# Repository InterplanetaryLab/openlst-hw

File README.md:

Interplanetary Initiative Lab Fork - OpenLST Reference Hardware
==========================
Due to the Qorvo Power Amplifier in the original design being deprecated, 
the power amplifier was swapped to the newer Qorovo RFFM6406. 
This was more of just a name change as the pinout is identical and the 
electrical specifications of both chips are nearly identical.

*Note - Gerbel files should not need to be updated *

OpenLST Reference Hardware
==========================

This repository contains a KiCad project with a hardware reference
implementation for the OpenLST.  This design is a simplified version
of the Texas Instruments CC1110 432 MHz reference design.  A 1 watt
power amplifier module has been added to increase operating range.
The design is intended for use at 437 MHz, however, it may be modified
for use at other frequencies.

The user is responsible for obtaining and maintaining the necessary
license to operate this radio.  The example project uses frequencies
in the US Amateur Radio UHF band. Transmissions in this band require a
valid FCC license and compliance with CFR Part 97.

Contents
--------

This repository contains the following items:

  * [KiCAD 4.0](http://kicad-pcb.org/) project with self-contained part library
  * [Schematic](pdf/openlst-hw.pdf) in PDF form
  * [Bill of materials](bom/) with ordering information for components
  * [Gerber files](gerber/) for PCB fabrication

License & Legal Information
---------------------------

Copyright 2018 Planet Labs Inc. This work is licensed under a
Creative Commons Attribution-ShareAlike 4.0 International License.

This document may contain technology or software the export of which
is or may be restricted by the Export Administration Act and the
Export Administration Regulations (EAR), 15 C.F.R. parts
730-774. Diversion contrary to U.S. law is prohibited.

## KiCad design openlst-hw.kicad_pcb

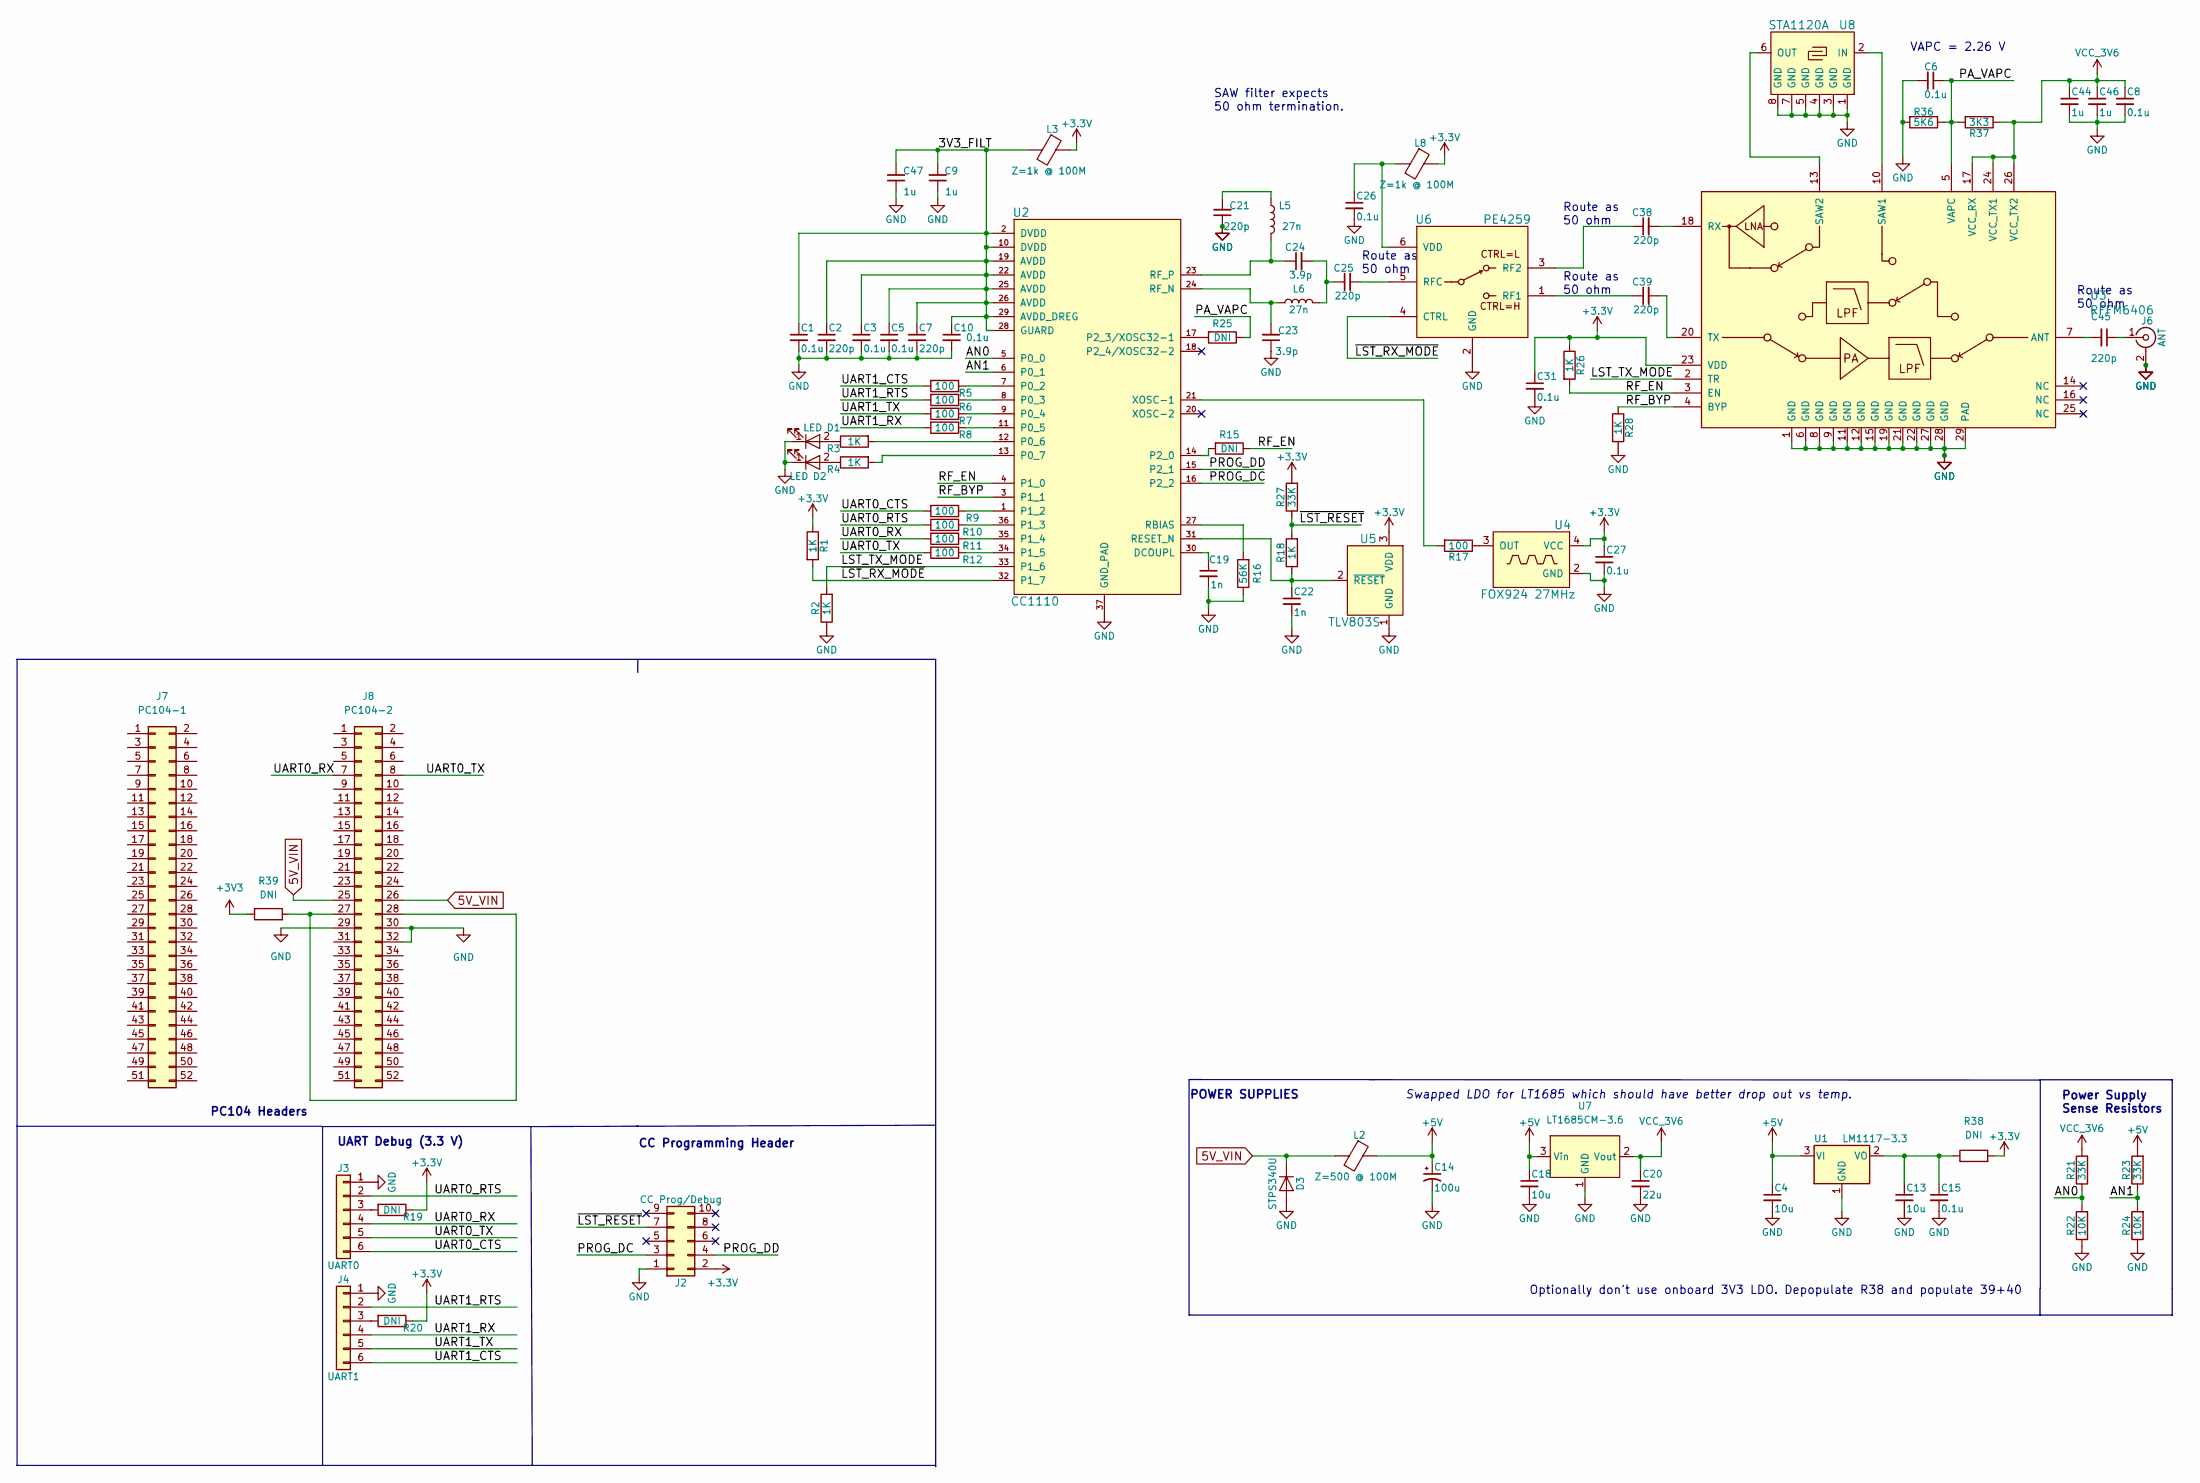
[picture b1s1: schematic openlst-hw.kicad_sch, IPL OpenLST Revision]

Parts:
C1, C3, C5, C6, C8, C10, C15, C26, C27, C31: 0.1u; C_0603_1608Metric; ManufPN 0603YC104K4T4A
C2, C7, C21, C25, C38, C39, C45: 220p; C_0402_1005Metric; ManufPN C0402C221J2GACAUTO
C4, C13, C18: 10u; C_0603_1608Metric; ManufPN GRT188C81A106ME13D
C9, C44, C46, C47: 1u; C_0603_1608Metric; ManufPN CL10B105MO8NNWC
C14: 100u; CP_EIA-3528-15_AVX-H; ManufPN TPSB107M010R0400
C19, C22: 1n; C_0603_1608Metric; ManufPN GCM188R71E102KA37D
C20: 22u; C_0603_1608Metric; ManufPN GRT188C81A106ME13D
C23, C24: 3.9p; C_0402_1005Metric; ManufPN GJM1555C1H3R9CB01D
D1: LED; LED_0603_1608Metric; ManufPN 150060VS75000
D2: LED; LED_0603_1608Metric; ManufPN 150060SS75000
D3: STPS340U; D_SMB; ManufPN STPS340U
J2: CC Prog/Debug; PinHeader_2x05_P1.27mm_Vertical_SMD; ManufPN FTSH-105-01-L-DV-K-P
J3: UART0; PinHeader_1x06_P2.54mm_Vertical; ManufPN 61300611121
J4: UART1; PinHeader_1x06_P2.54mm_Vertical; ManufPN 61300611121
J6: ANT; SMA_Amphenol_132134_Vertical; ManufPN 732511150
J7: PC104-1; PinSocket_2x26_P2.54mm_Vertical
J8: PC104-2; PinSocket_2x26_P2.54mm_Vertical
L2: Z=500 @ 100M; L_1206_3216Metric; ManufPN MI1206L501R-10
L3, L8: Z=1k @ 100M; L_0603_1608Metric; ManufPN 74279266
L5, L6: 27n; L_0402_1005Metric; ManufPN LQW15AN27NJ00D
R1, R2, R3, R4, R18, R26, R28: 1K; R_0603_1608Metric; ManufPN RC0603JR-071KL
R5, R6, R7, R8, R9, R10, R11, R12, R17: 100; R_0603_1608Metric; ManufPN AC0603FR-07100RL
R15, R19, R20, R25: DNI; R_0603_1608Metric
R16: 56K; R_0603_1608Metric; ManufPN RMCF0603FT56K0
R21, R23, R27: 33K; R_0603_1608Metric; ManufPN AC0603FR-0733KL
R22, R24: 10K; R_0603_1608Metric; ManufPN RC0603JR-0710KL
R36: 5K6; R_0603_1608Metric; ManufPN RMCF0603FT5K60
R37: 3K3; R_0603_1608Metric; ManufPN RMCF0603FT3K30
R38, R39: DNI; R_0603_1608Metric_Pad0.98x0.95mm_HandSolder
U1: LM1117-3.3; SOT-223-3_TabPin2; ManufPN LM1117IMP-3.3/NOPB
U2: CC1110; TI_CC_QFN36; ManufPN CC1110F32RHHR
U3: RFFM6406; Qorvo_LGA_28
U4: FOX924 27MHz; Oscillator_SMD_Fordahl_DFAS15-4Pin_5.0x3.2mm; ManufPN FT5HNBPK27.0-T1
U5: TLV803S; SOT-23; ManufPN TLV803SDBZR
U6: PE4259; SOT-363_SC-70-6; ManufPN 4259-63
U7: LT1685CM-3.6; TO-263-3_TabPin2
U8: STA1120A; SAW-8_3.8mm; ManufPN STA1120A

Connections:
5V_VIN: D3.1 (K), J8.25, J8.26, L2.2
+5V: C4.1, C14.1, C18.1, L2.1, R23.2, U1.3 (VI), U7.3 (Vin)
/3V3_FILT: C1.1, C2.1, C3.1, C5.1, C7.1, C9.2, C10.1, C47.2, L3.2, U2.2 (DVDD), U2.10 (DVDD), U2.19 (AVDD), U2.22 (AVDD), U2.25 (AVDD), U2.26 (AVDD), U2.28 (GUARD), U2.29 (AVDD_DREG)
/AN0: R21.1, R22.2, U2.5 (P0_0)
/AN1: R23.1, R24.2, U2.6 (P0_1)
/LST_TX_MODE: R2.2, U2.33 (P1_6), U3.2 (TR); also elsewhere on the board
/PA_VAPC: C6.1, R25.1, R36.1, R37.2, U3.5 (VAPC)
/PROG_DC: J2.3, U2.16 (P2_2)
/PROG_DD: J2.4, U2.15 (P2_1)
/RF_BYP: R28.1, U2.3 (P1_1), U3.4 (BYP)
/RF_EN: R15.1, R26.2, U2.4 (P1_0), U3.3 (EN)
/UART0_CTS: J3.6, R9.2
/UART0_RTS: J3.2, R10.2
/UART0_RX: J3.4, J8.7, R11.2
/UART0_TX: J3.5, J8.8, R12.2
/UART1_CTS: J4.6, R5.2
/UART1_RTS: J4.2, R6.2
/UART1_RX: J4.4, R8.2
/UART1_TX: J4.5, R7.2
/~LST_RESET: J2.7, R18.2, R27.1
/~LST_RX_MODE: R1.2, U2.32 (P1_7), U6.4 (CTRL); also elsewhere on the board
GND: C1.2, C2.2, C3.2, C4.2, C5.2, C6.2, C7.2, C8.2, C9.1, C10.2, C13.2, C14.2, C15.2, C18.2, C19.2, C20.2, C21.1, C22.2, C23.1, C26.2, C27.2, C31.2, C44.2, C46.2, C47.1, D1.1 (K), D2.1 (K), D3.2 (A), J2.1, J3.1, J4.1, J6.2 (Ext), J8.29, J8.30, J8.32, R2.1, R16.1, R22.1, R24.1, R28.2, R36.2, U1.1 (GND), U2.37 (GND_PAD), U3.1 (GND), U3.6 (GND), U3.8 (GND), U3.9 (GND), U3.11 (GND), U3.12 (GND), U3.15 (GND), U3.19 (GND), U3.21 (GND), U3.22 (GND), U3.27 (GND), U3.28 (GND), U3.29 (PAD), U4.2 (GND), U5.1 (GND), U6.2 (GND), U7.1 (GND), U8.1 (GND), U8.3 (GND), U8.4 (GND), U8.5 (GND), U8.7 (GND), U8.8 (GND); also elsewhere on the board
unnamed: C13.1, C15.1, R38.1, U1.2 (VO)
unnamed: C19.1, U2.30 (DCOUPL)
unnamed: C21.2, L5.1
unnamed: C22.1, R18.1, U2.31 (RESET_N), U5.2 (~RESET)
unnamed: C23.2, L6.1, U2.24 (RF_N)
unnamed: C24.1, L5.2, U2.23 (RF_P)
unnamed: C24.2, C25.1, L6.2
unnamed: C25.2, U6.5 (RFC)
unnamed: C26.1, L8.2, U6.6 (VDD)
unnamed: C38.1, U6.3 (RF2)
unnamed: C38.2, U3.18 (RX)
unnamed: C39.1, U6.1 (RF1)
unnamed: C39.2, U3.20 (TX)
unnamed: C45.1, J6.1 (In)
unnamed: C45.2, U3.7 (ANT)
unnamed: D1.2 (A), R3.1
unnamed: D2.2 (A), R4.1
unnamed: J3.3, R19.2
unnamed: J4.3, R20.2
unnamed: J8.27, J8.28, R39.2
unnamed: R3.2, U2.12 (P0_6)
unnamed: R4.2, U2.13 (P0_7)
unnamed: R5.1, U2.7 (P0_2)
unnamed: R6.1, U2.8 (P0_3)
unnamed: R7.1, U2.9 (P0_4)
unnamed: R8.1, U2.11 (P0_5)
unnamed: R9.1, U2.1 (P1_2)
unnamed: R10.1, U2.36 (P1_3)
unnamed: R11.1, U2.35 (P1_4)
unnamed: R12.1, U2.34 (P1_5)
unnamed: R15.2, U2.14 (P2_0)
unnamed: R16.2, U2.27 (RBIAS)
unnamed: R17.1, U4.3 (OUT)
unnamed: R17.2, U2.21 (XOSC-1)
unnamed: R25.2, U2.17 (P2_3/XOSC32-1)
unnamed: U3.10 (SAW1), U8.2 (IN)
unnamed: U3.13 (SAW2), U8.6 (OUT)
VCC_3V6: C8.1, C20.1, C44.1, C46.1, R21.2, R37.1, U3.17 (VCC_RX), U3.24 (VCC_TX1), U3.26 (VCC_TX2), U7.2 (Vout)

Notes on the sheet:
Power Supply Sense Resistors
Swapped LDO for LT1685 which should have better drop out vs temp.
Route as 50 ohm
VAPC = 2.26 V
PC104 Headers
SAW filter expects 50 ohm termination.
Optionally don't use onboard 3V3 LDO. Depopulate R38 and populate 39+40
POWER SUPPLIES
UART Debug (3.3 V)
CC Programming Header

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
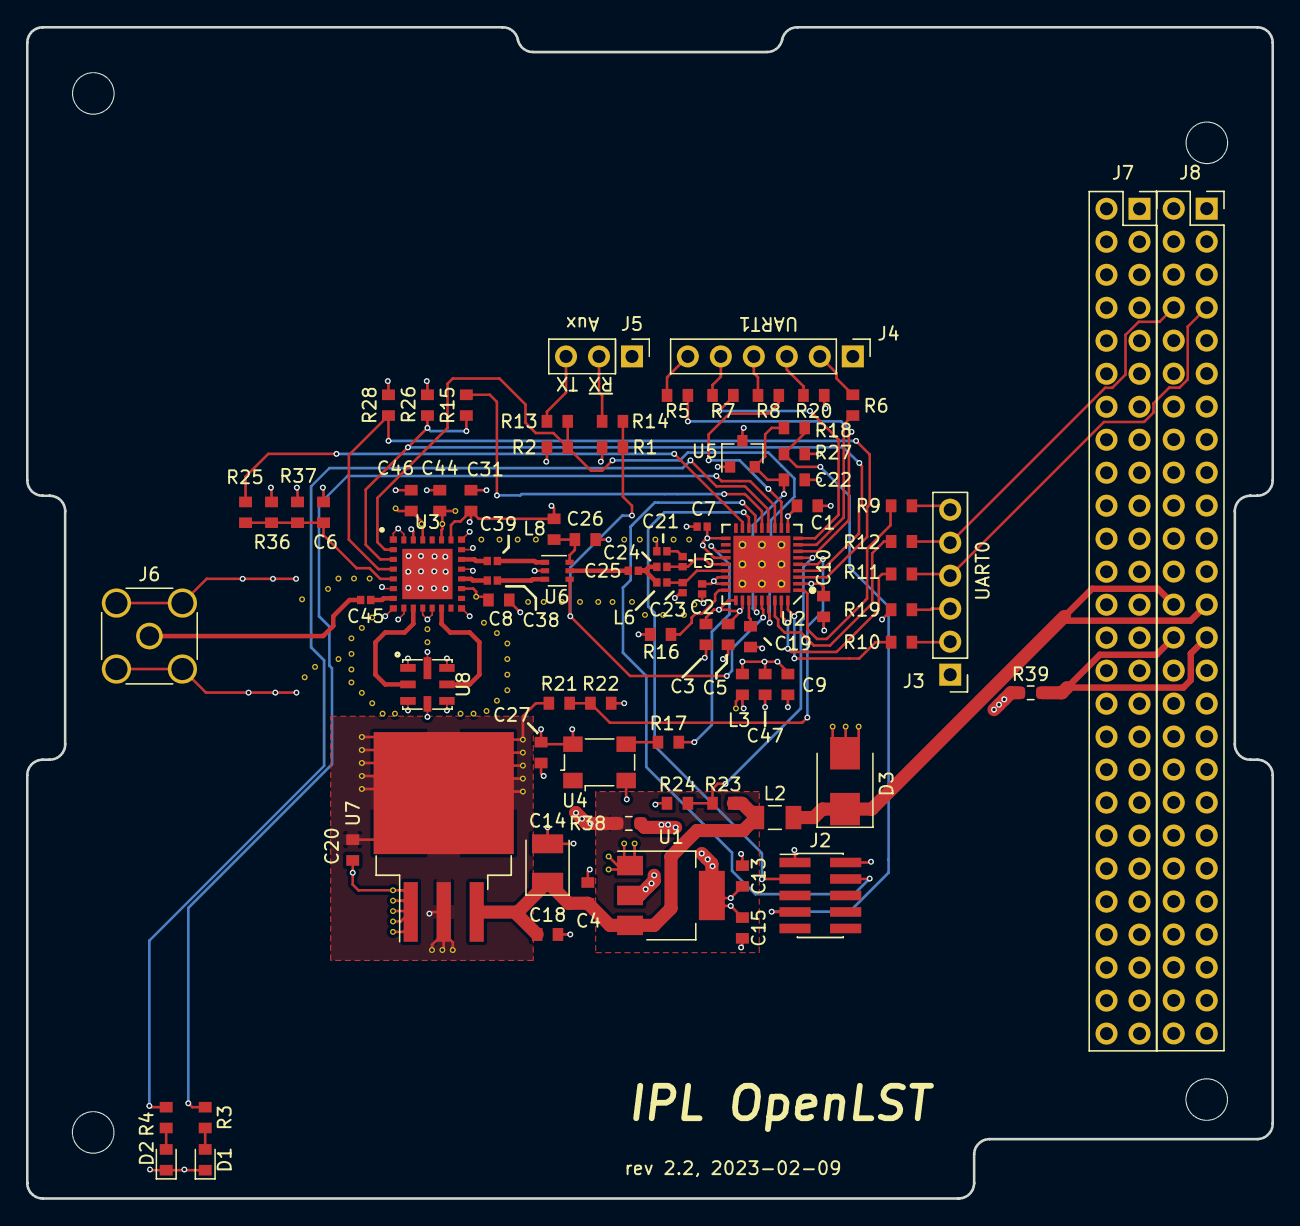
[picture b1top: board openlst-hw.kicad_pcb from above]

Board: 4 copper layers, 95.9 x 90.2 mm, 89 parts (0 on the bottom side), 63 nets.

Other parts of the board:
J5: Control Outputs; PinHeader_1x03_P2.54mm_Vertical
R13, R14: 100; R_0603_1608Metric
REF1, REF2, REF3, REF4: MountingHole_3.2mm_M3

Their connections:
/LST_TX_MODE: R13.1; also elsewhere on the board
/~LST_RX_MODE: R14.1; also elsewhere on the board
GND: J5.1; also elsewhere on the board
unnamed: J5.2, R14.2
unnamed: J5.3, R13.2

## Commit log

2021-06-03 updated schematic to use the newer qorvo power amplifier
2023-02-09 CAM: commiting v2.2 (inprogress) which makes the openlst board fit in a PC104 stack and swaps an ldo
2023-02-16 CAM: commiting current revision
2023-02-28 CAM: updated layout to fix some issues with ground plane arrangement
2023-03-02 CAM: updated schematic pdf
